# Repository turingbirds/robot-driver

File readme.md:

# Robot driver

Heavy duty 12 V servo motor driver with Wifi link

**⚠️ Status: prototype ⚠️**

https://user-images.githubusercontent.com/1014092/205401948-c3db500c-c33b-486b-9b15-0c6e07ba4ee2.mp4

## Features

- 3 bidirectional motor outputs (motors wired as H-bridge; 6 output channels in total)
- Wireless low-latency interface via UDP
- Battery powered with a 14.4 V Makita power tool battery
- Flexible I/O options for motor position encoders, servo motor drivers, etc.
- Hardware address pins allow multiple devices on a network
- Unity VR interface

## Tech

- ESP32 controller
- BTS7960 driver for each output channel
- Inrush current limiter via low-side series MOSFET

PCB fits the case of a Makita battery charger.

Bill of materials: [CSV](bom.csv)

## Benchmarking

### Motor driver

Supply rail transient response during the demo program (as in the video):

### Network

Each controller announces its presence by sending a UDP broadcast message containing its hardware address and IP address.

Packets containing control commands can then sent to a specific IP address, based on selecting a hardware address.

#### UDP network benchmarks for uncongested wifi

#### UDP network benchmarks for congested wifi

## License

[Open source hardware](https://www.oshwa.org/) is hardware for which the design is made publicly available, so that anyone can study, modify, distribute, make, and sell the design or hardware based on that design, subject to the following license conditions.

Hardware licensed under the *CERN Open Hardware Licence Version 2 - Weakly Reciprocal,* a copy of which is included in this repository at [cern_ohl_w_v2.txt](https://github.com/turingbirds/robot-driver/blob/master/cern_ohl_w_v2.txt).

Software licensed under the *Apache License 2.0,* a copy of which is included at [apache_license_2.0.txt](https://github.com/turingbirds/robot-driver/blob/master/apache_license_2.0.txt).

## Credits

This project was co-produced by V2_ Lab for the Unstable Media as part of the Winter Sessions art and technology residencies. ♥️

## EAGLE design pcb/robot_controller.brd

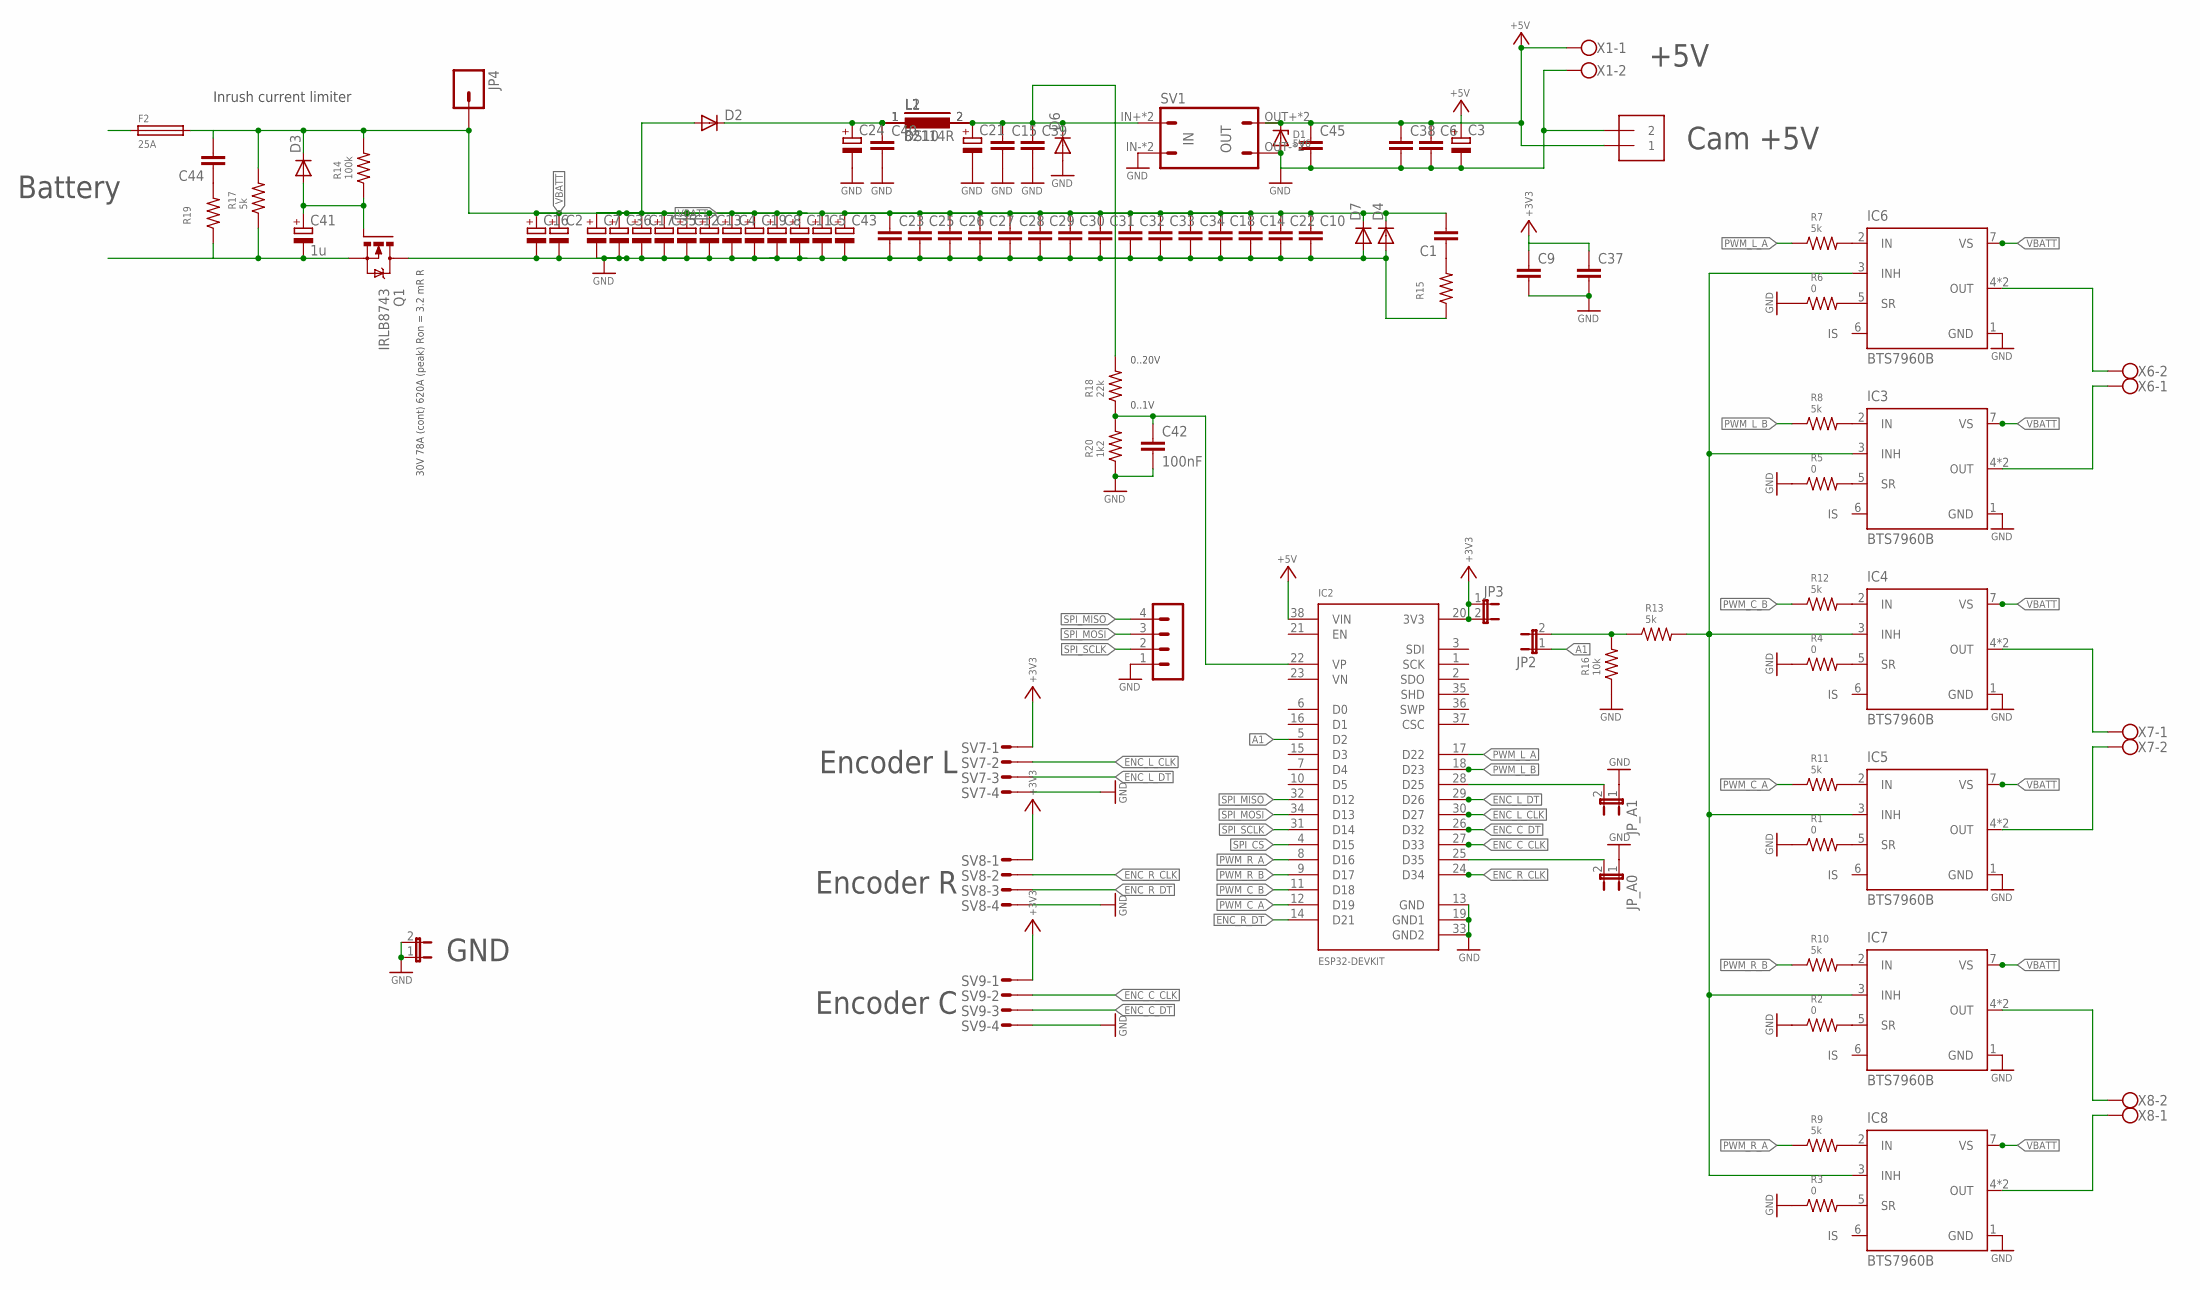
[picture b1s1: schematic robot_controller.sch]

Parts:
C1: C-EU025-025X050; C025-025X050
C2, C3, C4, C5, C7, C8, C11, C12, C13, C16, C17, C19, C21, C24, C35, C36, C43: CPOL-EUE5-10.5; E5-10,5
C6, C9, C10, C14, C15, C18, C22, C23, C25, C26, C27, C28, C29, C30, C31, C32, C33, C34, C37, C38, C39, C40, C45: C-EUC1206; C1206
C41: 1u; E2,5-6
C42: 100nF; C1206
C44: C-EU050-030X075; C050-030X075
D1: 5V6; DO41Z10
D2, D6: DIODE-DO15-12; DO15-12
D3: DIODE-DO-214AC; DO-214AC
D4, D7: DIODE-DO41-7.6; DO41-7.6
F2: 25A; SHK20L
IC2: ESP32-DEVKIT; DEVKIT-V1-NOHOLES
IC3, IC4, IC5, IC6, IC7, IC8: BTS7960B; P-TO263-7-1
J6: 1X2-3.5MM; 3.5MMTERM
JP1, JP2, JP3: JP1E; JP1
JP4: M01PTH_LONGPAD; 1X01_LONGPAD
JP_A0, JP_A1: JP1E; JP1
L1: 82114R
L2: DS10
Q1: IRLB8743; TO220BV
R1, R2, R3, R4, R5, R6: 0; R1206
R7, R8, R9, R10, R11, R12, R13, R17: 5k; R1206
R14: 100k; R1206
R15: R-US_0411/3V; 0411V
R16: 10k; R1206
R18: 22k; R1206
R19: R-US_0617/5V; 0617V
R20: 1k2; R1206
SV1: MA04-1SMALL; MA04-2
SV6: MA04-1
SV7, SV8, SV9: MT6-4
X1, X6, X7, X8: W239-302

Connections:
+3V3: C9.1, C37.1, IC2.20 (3V3), JP3.1, JP3.2, SV7.1, SV8.1, SV9.1
+5V: C3.+, C6.1, C38.1, C45.1, D1.C, IC2.38 (VIN), J6.1, SV1.OUT+, SV1.OUT+1 (OUT+), X1.1
A1: IC2.5 (D2), JP2.1
ENC_C_CLK: IC2.27 (D33), SV9.2
ENC_C_DT: IC2.26 (D32), SV9.3
ENC_L_CLK: IC2.30 (D27), SV7.2
ENC_L_DT: IC2.29 (D26), SV7.3
ENC_R_CLK: IC2.24 (D34), SV8.2
ENC_R_DT: IC2.14 (D21), SV8.3
GND: C2.-, C3.-, C4.-, C5.-, C6.2, C7.-, C8.-, C9.2, C10.2, C11.-, C12.-, C13.-, C14.2, C15.2, C16.-, C17.-, C18.2, C19.-, C21.-, C22.2, C23.2, C24.-, C25.2, C26.2, C27.2, C28.2, C29.2, C30.2, C31.2, C32.2, C33.2, C34.2, C35.-, C36.-, C37.2, C38.2, C39.2, C40.2, C42.2, C43.-, C45.2, D1.A, D4.A, D6.A, D7.A, IC2.13 (GND), IC2.19 (GND1), IC2.33 (GND2), IC3.1 (GND), IC4.1 (GND), IC5.1 (GND), IC6.1 (GND), IC7.1 (GND), IC8.1 (GND), J6.2, JP1.1, JP1.2, JP_A0.1, JP_A1.1, Q1.D, R1.1, R2.1, R3.1, R4.1, R5.1, R6.1, R15.1, R16.1, R20.1, SV1.IN-, SV1.IN-1 (IN-), SV1.OUT-, SV1.OUT-1 (OUT-), SV6.1, SV7.4, SV8.4, SV9.4, X1.2
unnamed: C24.+, C40.1, D2.C, L1.1, L2.1
unnamed: IC7.4 (OUT), IC7.8 (OUT), X8.2
unnamed: IC7.5 (SR), R2.2
unnamed: IC8.4 (OUT), IC8.8 (OUT), X8.1
unnamed: IC5.4 (OUT), IC5.8 (OUT), X7.2
unnamed: IC4.4 (OUT), IC4.8 (OUT), X7.1
unnamed: F2.1A (1), F2.1B (1)
unnamed: IC2.28 (D25), JP_A1.2
unnamed: IC3.4 (OUT), IC3.8 (OUT), X6.1
unnamed: IC6.4 (OUT), IC6.8 (OUT), X6.2
unnamed: IC5.5 (SR), R1.2
unnamed: IC8.5 (SR), R3.2
unnamed: IC4.5 (SR), R4.2
unnamed: C15.1, C21.+, C39.1, D6.C, L1.2, L2.2, R18.2, SV1.IN+, SV1.IN+1 (IN+)
unnamed: IC3.5 (SR), R5.2
unnamed: IC6.5 (SR), R6.2
unnamed: IC3.3 (INH), IC4.3 (INH), IC5.3 (INH), IC6.3 (INH), IC7.3 (INH), IC8.3 (INH), R13.2
unnamed: IC6.2 (IN), R7.2
unnamed: IC4.2 (IN), R12.2
unnamed: IC5.2 (IN), R11.2
unnamed: IC7.2 (IN), R10.2
unnamed: IC8.2 (IN), R9.2
unnamed: IC3.2 (IN), R8.2
unnamed: C1.1, R15.2
unnamed: JP2.2, R13.1, R16.2
unnamed: IC2.25 (D35), JP_A0.2
unnamed: C41.+, D3.A, Q1.G, R14.1
unnamed: C41.-, Q1.S, R17.1, R19.1
unnamed: C42.1, IC2.22 (VP), R18.1, R20.2
unnamed: C44.1, R19.2
PWM_C_A: IC2.12 (D19), R11.1
PWM_C_B: IC2.11 (D18), R12.1
PWM_L_A: IC2.17 (D22), R7.1
PWM_L_B: IC2.18 (D23), R8.1
PWM_R_A: IC2.8 (D16), R9.1
PWM_R_B: IC2.9 (D17), R10.1
SPI_CS: IC2.4 (D15)
SPI_MISO: IC2.32 (D12), SV6.4
SPI_MOSI: IC2.34 (D13), SV6.3
SPI_SCLK: IC2.31 (D14), SV6.2
VBATT: C1.2, C2.+, C4.+, C5.+, C7.+, C8.+, C10.1, C11.+, C12.+, C13.+, C14.1, C16.+, C17.+, C18.1, C19.+, C22.1, C23.1, C25.1, C26.1, C27.1, C28.1, C29.1, C30.1, C31.1, C32.1, C33.1, C34.1, C35.+, C36.+, C43.+, C44.2, D2.A, D3.C, D4.C, D7.C, F2.2A (2), F2.2B (2), IC3.7 (VS), IC4.7 (VS), IC5.7 (VS), IC6.7 (VS), IC7.7 (VS), IC8.7 (VS), JP4.1, R14.2, R17.2

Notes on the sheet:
GND
Battery
Encoder L
Encoder R
Encoder C
Cam +5V
+5V
Inrush current limiter
30V 78A (cont) 620A (peak) Ron = 3.2 mR R
0..20V
0..1V

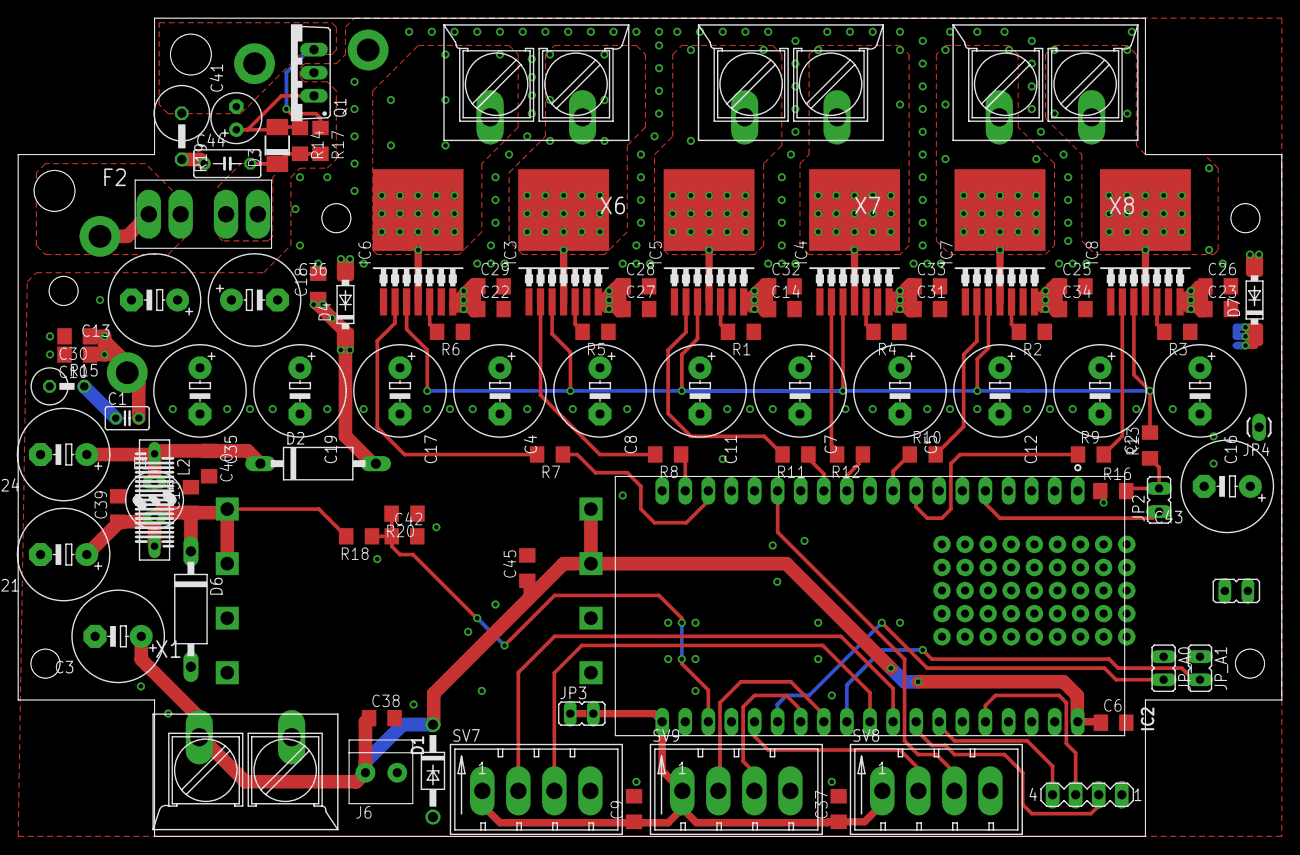
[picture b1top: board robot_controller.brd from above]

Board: 2 copper layers, 139.0 x 90.0 mm, 97 parts (0 on the bottom side), 50 nets.

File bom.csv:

Qty,Identifier,Description,Value,Package,,Price/1,Price (tot)
,,,,,,,
6,"R1, R2, R3, R4, R5, R6",Resistor 0 Ohm,,1206,,0.05,
8,"R7, R8, R9, R10, R11, R12, R13, R17",Resistor 5k Ohm,,1206,,0.05,
1,R14,Resistor 100k Ohm,,1206,,0.05,
2,"R15, R19",Resistor 100 Ohm 1 W,,through-hole,,0.25,
1,R16,Resistor 10k Ohm,,1206,,0.05,
1,R18,Resistor 22k Ohm,,1206,,0.05,
1,R20,Resistor 1.2k Ohm,,1206,,0.05,
,,,,,,,
1,C41,Electrolytic capacitor,"1 uF, 63V","through-hole, E2.5-6",,0.25,
2,"C1, C44",Ceramic capacitor,"10 nF, 63 V",through-hole,,0.25,
14,"C2, C3, C4, C5, C7, C8, C11, C12, C13, C16, C17, C19, C21, C24, C35, C36, C43",Electrolytic capacitor,"470 uF, 35 V","through-hole, E5-10.5",,0.68,9.47
23,"C6, C9, C10, C14, C15, C18, C22, C23, C25, C26, C27, C28, C29, C30, C31, C32, C33, C34, C37, C38, C39, C40, C42",Ceramic capacitor (MLCC),"100 nF, 25 V",1206,,0.05,
,,,,,,,
1,L1,EMI suppression inductor (optional),,,,,
,,,,,,,
1,D1,5V6 zener diode,1N5339,DO41,,0.3,0.3
1,"D2, D6",Schottky diode,,DO15-12,,,
1,D3,Schottky diode,,DO214,,,
2,"D4, D7",TVS diode,P6KE22A,DO41-7.6,,0.49,0.98
,,,,,,,
1,SV6,IDC header 4-pin,,,,,
3,"SV7, SV8, SV9",Screw terminals 4 mm pitch,,,,0.12,0.36
4,"X1, X6, X7, X8",Screw terminals 10 mm pitch,,,,0.18,0.72
1,,jumper,,,,,
3,"JP1, JP2, JP3",IDC header 2-pin,,,,,
1,,Socket for ESP32 (2x 19 pin female IDC),,,,,
,J6,Header (optional),,,,,
,,,,,,,
1,IC2,ESP32-DEVKIT,,,,5,5
1,Q1,IRLB8743 n-MOSFET,,TO220,,3.92,3.92
6,"IC3, IC4, IC5, IC6, IC7, IC8",BTS7960B,,TO263-7,,1.44,8.62
1,SV1,5V buck converter,,,,0.8,0.8
,,,,,,,
1,,Heatsink 20x108 mm,,,,0.75,0.75
1,,Thermal pad 20x108 mm,,,,2.33,2.33
1,,5V DC fan 20 or 25 mm (optional),,,,,
1,F2,Mini car fuse + holder,,,,0.15,0.15
1,,Enclosure,,,,,

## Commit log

2022-12-01 add esp32
2022-12-01 add pcb
2022-12-01 add readme
2022-12-05 add licenses
2022-12-05 add license to readme
2022-12-22 controller reports on battery voltage
2022-12-23 add bill of materials
2023-01-01 update BOM
2023-01-12 fix drill sizes on PCB
2023-02-12 add manual control test script
2023-02-12 add jumpers to the PCB for setting the address
2023-02-21 simplify directories hierarchy
2023-02-21 add support for controlling small normal servo motors
2023-02-22 fix auxiliary servo motor control
2023-02-26 add support for aux servos
2023-02-28 optimized MQTT messaging and handling
2023-03-07 add exercise mode
2023-06-24 add UDP benchmarks
2023-06-24 add Unity VR interface
2023-06-24 changed MQTT to UDP interface
2023-06-28 prevent manual controller script from triggering timeout safety
2023-06-30 add ESP32 header to BOM
2023-07-10 add GND and +12V tap points to the controller PCB
2023-08-19 allow multiple robots per network
2023-08-19 add pcb photo
2023-08-19 add photo to readme
2023-08-21 increase timeout delay on UDP broadcast disconnect
2023-08-21 clean up wifi
2023-08-25 fix pull-up on switches and low-pass filtering
